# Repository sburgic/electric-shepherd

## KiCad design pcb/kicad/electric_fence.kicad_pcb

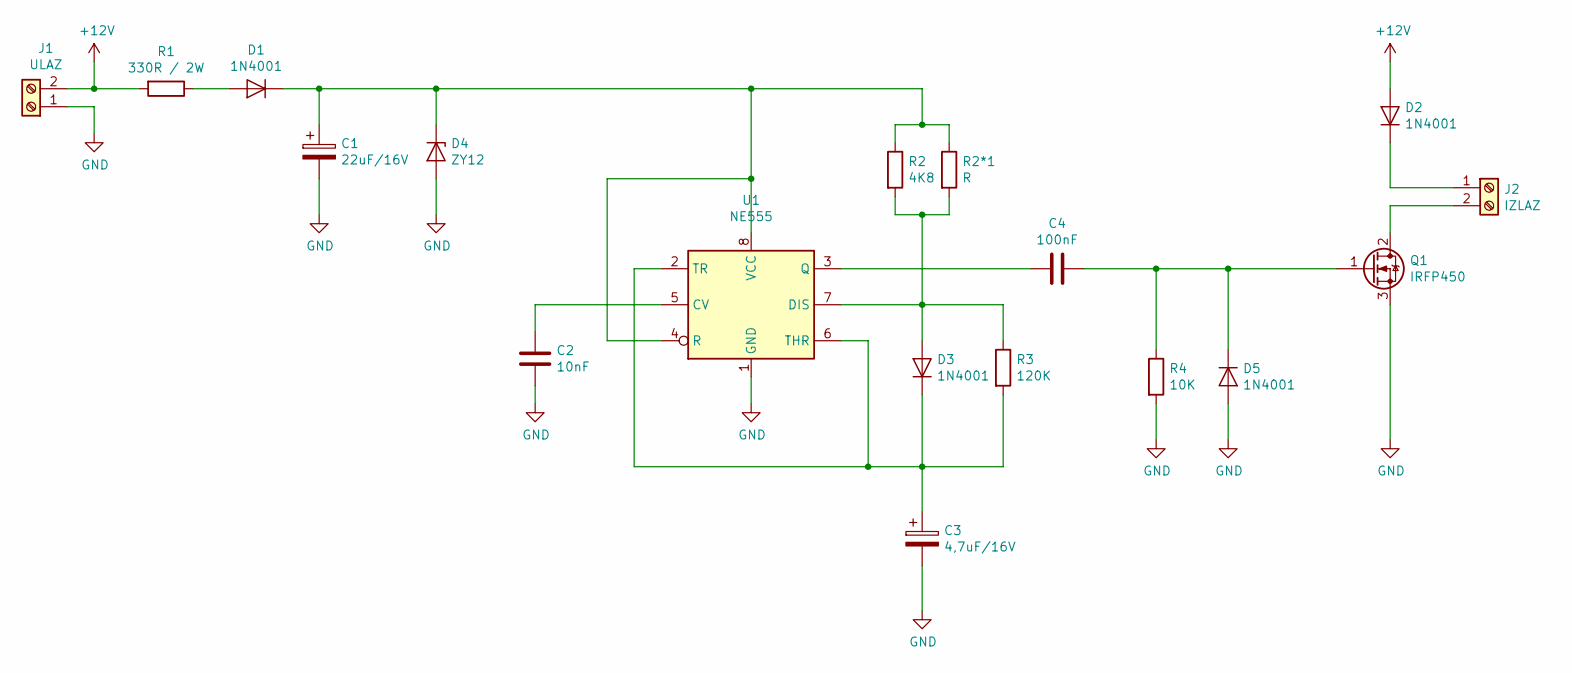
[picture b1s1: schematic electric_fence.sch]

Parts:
C1: 22uF/16V; CP_Radial_D5.0mm_P2.00mm
C2: 10nF; C_Rect_L4.0mm_W2.5mm_P2.50mm
C3: 4,7uF/16V; CP_Radial_D5.0mm_P2.00mm
C4: 100nF; C_Rect_L4.0mm_W2.5mm_P2.50mm
D1, D2, D3, D5: 1N4001; D_DO-41_SOD81_P10.16mm_Horizontal
D4: ZY12; D_DO-41_SOD81_P10.16mm_Horizontal
J1: ULAZ; TerminalBlock_RND_205-00045_1x02_P5.00mm_Horizontal
J2: IZLAZ; TerminalBlock_RND_205-00045_1x02_P5.00mm_Horizontal
Q1: IRFP450; TO-247-3_Vertical
R1: 330R / 2W; R_Axial_DIN0414_L11.9mm_D4.5mm_P15.24mm_Horizontal
R2: 4K8; R_Axial_DIN0207_L6.3mm_D2.5mm_P10.16mm_Horizontal
R2*1: R; R_Axial_DIN0207_L6.3mm_D2.5mm_P10.16mm_Horizontal
R3: 120K; R_Axial_DIN0207_L6.3mm_D2.5mm_P10.16mm_Horizontal
R4: 10K; R_Axial_DIN0207_L6.3mm_D2.5mm_P10.16mm_Horizontal
U1: NE555; DIP-8_W7.62mm

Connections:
+12V: D2.2 (A), J1.2, R1.2
GND: C1.2, C2.2, C3.2, D4.2 (A), D5.2 (A), J1.1, Q1.3 (S), R4.2, U1.1 (GND)
unnamed: C1.1, D1.1 (K), D4.1 (K), R2.1, R2*1.1, U1.4 (R), U1.8 (VCC)
unnamed: C2.1, U1.5 (CV)
unnamed: C3.1, D3.1 (K), R3.2, U1.2 (TR), U1.6 (THR)
unnamed: C4.1, D5.1 (K), Q1.1 (G), R4.1
unnamed: C4.2, U1.3 (Q)
unnamed: D1.2 (A), R1.1
unnamed: D2.1 (K), J2.1
unnamed: D3.2 (A), R2.2, R2*1.2, R3.1, U1.7 (DIS)
unnamed: J2.2, Q1.2 (D)

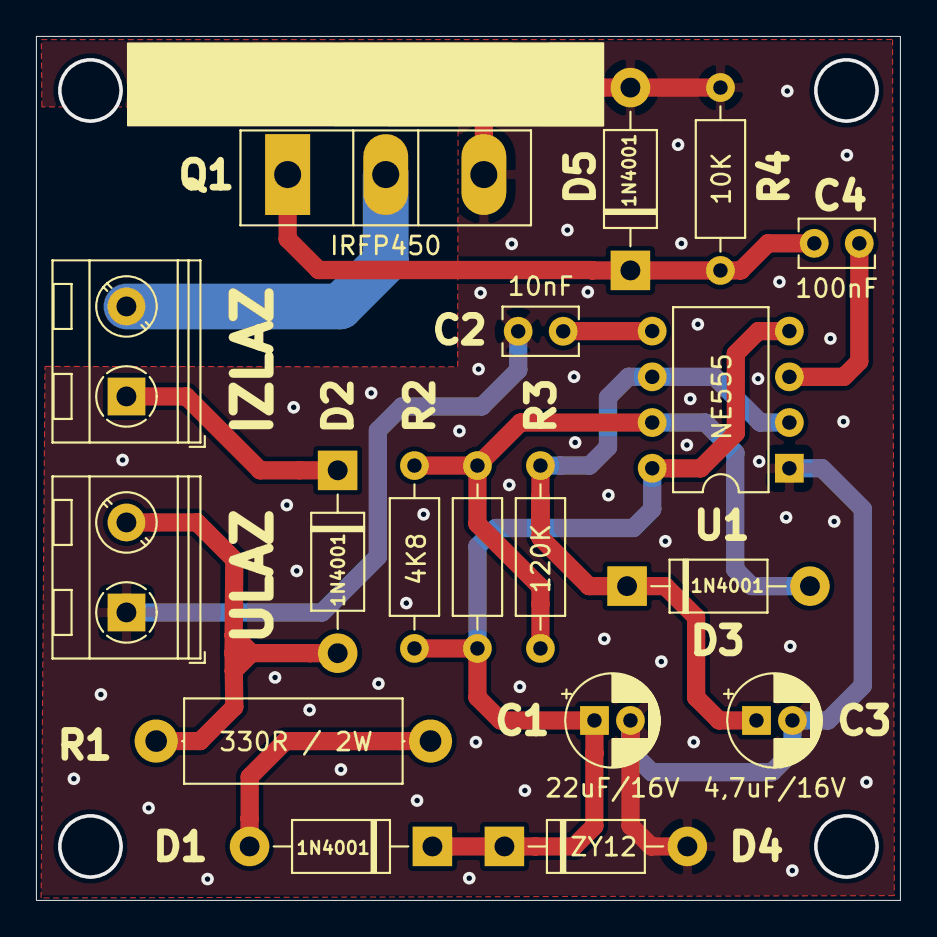
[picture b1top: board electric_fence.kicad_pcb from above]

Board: 2 copper layers, 48.0 x 48.0 mm, 18 parts (0 on the bottom side), 11 nets.

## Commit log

2020-09-03 add pcb ver 1.1
